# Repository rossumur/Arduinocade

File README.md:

#Arduinocade
Play retro color 8 bit games on your TV from an Arduino.

**Arduinocade** features old school color 8 bit graphics (tiles, sprites, smooth scrolling, simple 3D) and sound (4 voice wavetable synthesis). All video and audio signals are generated with three resistors, an upgraded crystal and a little software. By overclocking the Arduino to 28.6363Mhz we can directly manipulate NTSC to generate 27 simultaneous colors. An IR receiver supports a wide variety of keyboards, joysticks and remote controls.

Video of Arduinocade in action at https://www.youtube.com/watch?v=nGIujZiEu_o

##Games
These games are sketches of what is possible on the Arduinocade hardware and a far from the polished pieces that inspired them.

###Ballblaster
A one-on-one sports style game inspired by the brilliant 1984 game Ballblazer. This uses a simple physics model and a 2D/3D rendering pipeline to produce 60fps animation. Try and grab the ball and shoot it into your opponent's goal.

###Pacman
What can I say? pakku pakku pakku.

###Jowst
Fly around on ostrich thingys. Poke each other with sticks. Nice example of using the sprite engine to generate lots of large multicolor sprites.

###Caverns of Titan
Homage to the Atari classic “Caverns of Mars”. Smooth scrolling, sprites and animation.

##Building the Hardware
Lots of different ways to build this beastie. The design is simple enough to build on a breadboard with a DIP Atmega328, alternatively you might want to add a 28.6363Mhz crystal to a $2 Arduino Pro Mini or even build on a custom PCB. 

###You will need
+ Arduino Pro Mini, Atmega328p or equivalent
+ 28.6363Mhz Crystal (from Adafruit, eBay etc)
+ RCA Audio/Video Cable (eBay)
+ 470ohm, 1k and 100k resistors
+ IR receiver TSOP38238,TSOP4838 or equivalent (Adafruit, Mouser etc)
+ IR Input device (see below)

```
        +----------------+
        |    arduino     |
        |    uno/pro     |
        |     28Mhz      |       5v <--+-+   IR Receiver
        |                |      GND <--|  )  TSOP4838
        |              8 |-------------+-+
        |                |
        |              6 |----[ 100k ]--------> AUDIO
        |                |
        |              9 |----[  1k  ]----+---> VIDEO
        |                |                |
        |              1 |----[ 470  ]----+
        |                |
        |              3 |
        |              2 |
        |                |
        +----------------+
```

###Mini Pro

We will be upgrading the crystal/resonator on these boards from 16Mhz to 28.6363Mhz. The easiest ones to modify have the big silver cans on them. Others use a ceramic resonator which require a bit of SMD fiddling.

###Custom PCB

If you want to get silly and build a custom board you can get a video console down to about the size of a quarter. Board and schematics can be found in `sim/docs/eagle`.

##Input Devices

*Retcon IR Controller, Atari Flashback 4 joysticks, Apple TV remote*

A number of IR input devices are supported. The IR Wireless Controllers from Atari Flashback 4 work well and have that classic joystick feel, as do the Retron IR controllers. These can be readily found on eBay for a few bucks. The Apple TV remote is also supported by you might feel a little silly. Edit config.h to select your input of choice.

##Upgrading the bootloader
If you want to use the Arduino IDE you should upgrade the bootloader to be able to work at 115200 baud with the faster crystal installed. The optiboot_atmega32_28.hex image has been rebuilt with F_CPU=28636363 and a slower watchdog reset so baud rate calculations will be correct for our overclocked device. Install the image with avrdude and your favorite ISP.
```
avrdude -c usbtiny -p atmega328p -e -u -U lock:w:0x3f:m -U efuse:w:0x05:m -U hfuse:w:0xDE:m -U lfuse:w:0xFF:m
avrdude -c usbtiny -p atmega328p -U flash:w:optiboot_atmega328_28Mhz.hex -U lock:w:0x0f:m
```
Once the modified optiboot is installed the device will behave like an Uno, so remember to select that from the boards menu in the Arduino IDE.

##Using the Arduino IDE

>**Note:**
>The current code does not work correctly with Arduino IDEs later than 1.5.6. Compiler optimizations in later versions interfere with hand timed loops in the video kernels. I will fix soon.

Copy the `Arduinocade` folder into the IDE libraries folder and relaunch IDE. You should be able to open the example games from *File->Examples->Arduinocade*. Edit the config.h file to enable or disable the custom `BALLBLASTER_GAME` kernel.

##How it works

###Video
Upgrading the crystal to 28.6363Mhz allows us to run at a multiple (8x CPU clock, 4x SPI output) of the NTSC subcarrier frequency. By spitting out bits in the right pattern at the right time we can generate NTSC colorburst and different colors based on the relative phase of the pattern.

Black (0000), White (1111), gray_5 (0101) and gray_10 (1010) don’t have a chroma component; the other 12 colors do. By inserting or skipping an extra nop in rendering kernel we can select between two different phases at the start of a line yielding 12+12+(black,white,gray) = 27 simultaneous colors on screen simultaneously. You can then add more by dithering etc.

###The Art of Artifacts

*Left - Pixels being emitted from the TX port, Right - Colors as they appear on NTSC* 

Every HSYNC interrupt the cpu emits a 3.57Mhz colorburst signal then sends pixel data from carefully timed tile or RLE video kernels. These are tricky to maintain in C, as helpful compiler optimizations often alter timing in unexpected ways. They probably all need to move to asm at some point. See note above.

The higher layer code uses a RLE format (BallBlaster) or tiles to represent game content. Because we don’t have enough memory for a full frame buffer individual lines of tiles and sprites are composed in a loop that is in lock step with the HSYNC interrupt.

TileGrind is a primitive html/javascript tool for generating color tiles and sprites. It can load and save C structs and understands the nature of NTSC color phase / artifacting. Its limitations vividly recreate the frustration of early graphics editing tools.

###Audio
The Audio driver has two parts.  The low level kernel runs every HSYNC, stepping each of the 4 voices though it’s wavetable, mixing the sampled voices together based on their current volume and emitting a sample to the PWM/resistor single bit DAC. This corresponds to a sample rate of 15734Hz.

The high level task runs every frame at 60Hz and adjusts envelope, modulates frequency of the underlying channels etc. It is responsible for parsing data structures containing music tracks and sound effects, adjusting volume envelopes and frequencies, swapping wavetables for different instruments etc.

AudioGrind is a primitive html/javascript audio editing tool is used to convert midi files to C struct data. It can also be used to reverse engineer classic gaming sound effects using a graphical spectrogram, without which it is nearly impossible to figure out how the effects are constructed - I’m talking to you Joust.

###IR input Joysticks, Keyboards etc
The GPIO attached to the IR sensor is sampled at HSYNC and fed to one of a number of IR decoders. The 15734Hz sample rate is enough to accurately parse nearly all IR protocols. For performance reasons only one is enabled at a time; check the #ifdefs in ir_input.cpp.

##So enjoy

Let me know if you have some fun with it.

Cheers
Rossum

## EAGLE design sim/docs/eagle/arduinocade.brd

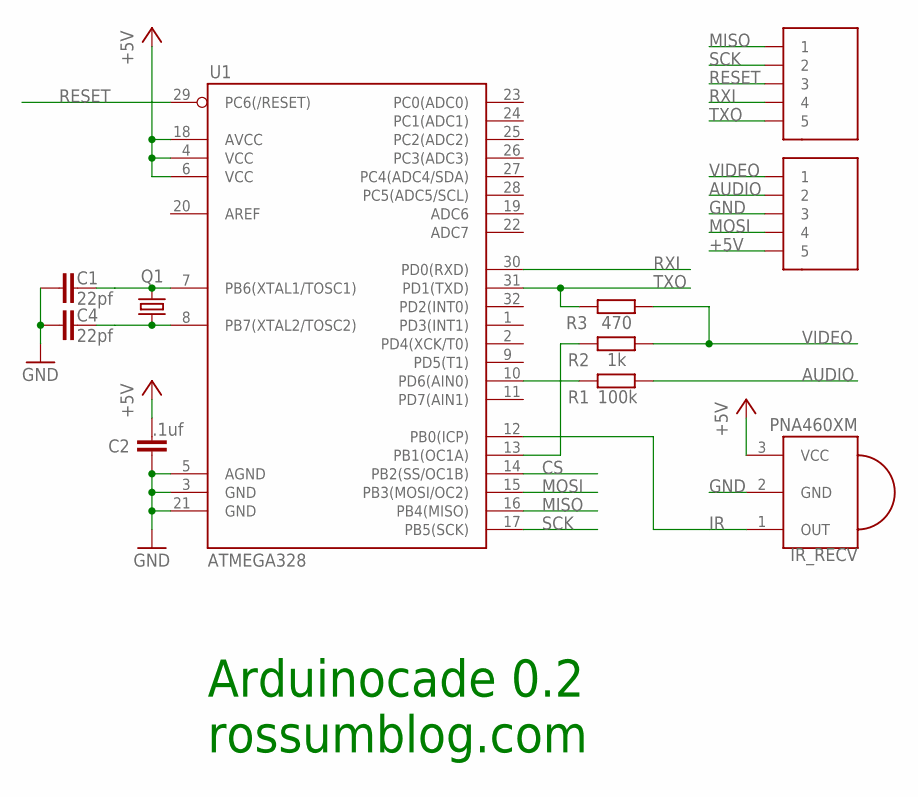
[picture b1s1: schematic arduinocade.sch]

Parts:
C1, C4: 22pf; C0603
C2: .1uf; C0603
IR_RECV: PNA460XM
Q1: CRYSTALCTS406; CTS406
R1: 100k; R0603
R2: 1k; R0603
R3: 470; R0603
U1: ATMEGA328; TQFP32-08
U$2, U$3: EDGE5

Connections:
+5V: C2.1, U1.4 (VCC), U1.6 (VCC), U1.18 (AVCC), U$3.5
AUDIO: R1.2, U$3.2
CS: U1.14 (PB2(SS/OC1B))
GND: C1.2, C2.2, C4.2, IR_RECV.2 (GND), U1.3 (GND), U1.5 (AGND), U1.21 (GND), U$3.3
IR: IR_RECV.1 (OUT), U1.12 (PB0(ICP))
MISO: U1.16 (PB4(MISO)), U$2.1
MOSI: U1.15 (PB3(MOSI/OC2)), U$3.4
unnamed: C4.1, Q1.1, U1.8 (PB7(XTAL2/TOSC2))
unnamed: C1.1, Q1.3 (2), U1.7 (PB6(XTAL1/TOSC1))
unnamed: R2.1, U1.13 (PB1(OC1A))
unnamed: R1.1, U1.10 (PD6(AIN0))
RESET: U1.29 (PC6(/RESET)), U$2.3
RXI: U1.30 (PD0(RXD)), U$2.4
SCK: U1.17 (PB5(SCK)), U$2.2
TXO: R3.1, U1.31 (PD1(TXD)), U$2.5
VCC: IR_RECV.3 (VCC)
VIDEO: R2.2, R3.2, U$3.1

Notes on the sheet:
Arduinocade 0.2
rossumblog.com

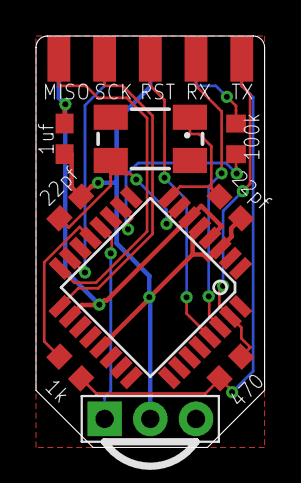
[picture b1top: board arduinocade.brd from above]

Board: 2 copper layers, 12.7 x 22.9 mm, 11 parts (1 on the bottom side), 15 nets.

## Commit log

2015-09-14 Arduinocade initial checkin
2015-09-15 Adding docs
2015-09-15 Doc tweaks
2015-09-15 More doc tweaks
2015-09-15 Additional images
2015-09-16 Add video link
2015-09-16 Tweak pacman
2015-09-17 Add pacman death scene
